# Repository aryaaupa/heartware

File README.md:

# heartware ♥

Heartware is being developed as a custom PCB with real-time audio playback, programmable lighting, sensing, battery power, and low-power firmware. The physical gift is intended to play a user-supplied local copy of **“The Man Who Can't Be Moved” by The Script**; the copyrighted recording is intentionally **not** distributed in this repository. This project will be used to demonstrate basic engineering principles to high schoolers. 

## Project goals

- Heart-shaped custom PCB with the electronics integrated into the board
- ESP32-S3-class embedded controller
- I²S digital audio path and Class-D speaker amplifier
- Local audio playback from flash storage
- Addressable RGB LED perimeter with audio-reactive animation
- Capacitive-touch interaction
- IMU-based pick-up / motion wake behavior
- Li-ion/LiPo battery, charging, battery monitoring, and USB-C power
- Hardware power switch and low-power states
- Debug/test points for board bring-up
- KiCad design sources, BOM, manufacturing outputs, firmware, and validation documentation

## Repository structure

```text
hardware/        KiCad board and schematic sources
firmware/        Embedded firmware and audio pipeline
manufacturing/   BOM / fabrication documentation
docs/            Architecture, bring-up, and validation notes
assets/private/  LOCAL-ONLY audio assets; ignored by Git
```

## Audio asset policy

The public repository contains no copyrighted song recording. A locally obtained audio file can be placed at:

```text
assets/private/song.wav
```

That directory is excluded by `.gitignore`. The firmware/build pipeline will be developed to preprocess and embed or stream the local asset without committing it.

## Status

**Rev A** is the initial KiCad prototype and uses a simpler XIAO ESP32-C3 + I²S amplifier architecture. **Rev B** is the planned advanced redesign described above and will replace the prototype architecture before fabrication.

> Do not fabricate Rev A yet. Footprints, power design, battery circuitry, audio chain, and Rev B architecture still require design review and DRC/ERC validation.

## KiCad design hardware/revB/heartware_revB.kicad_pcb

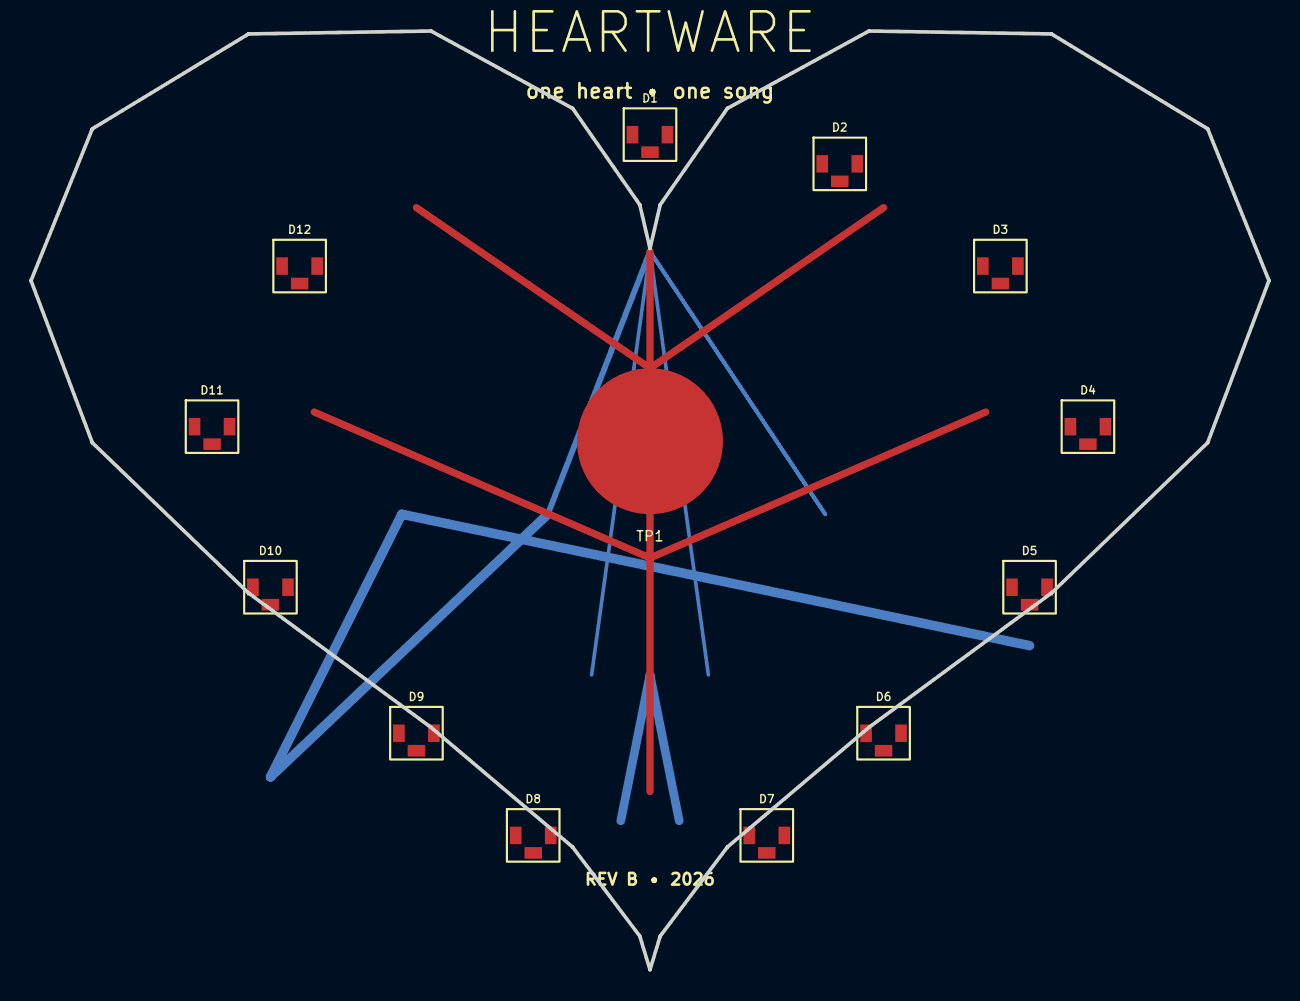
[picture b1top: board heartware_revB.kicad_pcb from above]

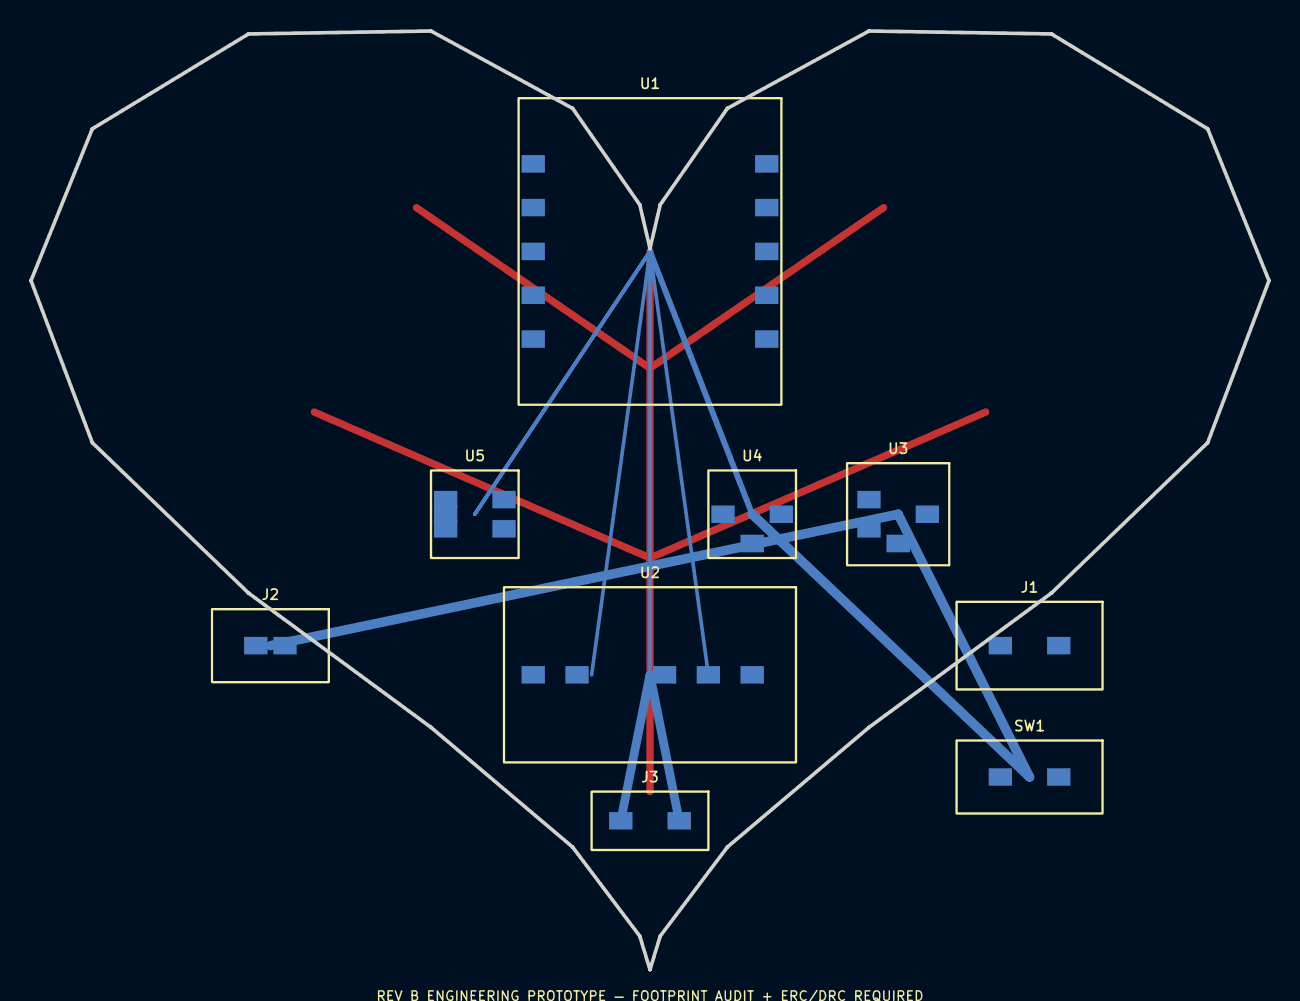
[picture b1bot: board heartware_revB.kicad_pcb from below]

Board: 4 copper layers, 84.8 x 64.3 mm, 22 parts (9 on the bottom side), 14 nets.

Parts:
D1: D1
D2: D2
D3: D3
D4: D4
D5: D5
D6: D6
D7: D7
D8: D8
D9: D9
D10: D10
D11: D11
D12: D12
J1: USB-C CHARGE; J1
J2: LIPO; J2
J3: SPEAKER; J3
SW1: POWER; SW1
TP1: TOUCH
U1: XIAO ESP32-S3; U1
U2: MAX98357A; U2
U3: MCP73871; U3
U4: TPS63031; U4
U5: LIS3DH; U5

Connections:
3V3: U1.3V3, U4.3V3, U5.3V3
BAT+: J2.+, U3.BAT
GND: D1.G, D2.G, D3.G, D4.G, D5.G, D6.G, D7.G, D8.G, D9.G, D10.G, D11.G, D12.G, J1.G, J2.-, U1.GND, U2.GND, U3.G, U4.G, U5.G
I2C_SCL: U1.SCL, U5.SCL
I2C_SDA: U1.SDA, U5.SDA
I2S_BCLK: U1.BCLK, U2.BCLK
I2S_DOUT: U1.DOUT, U2.DIN
I2S_WS: U1.WS, U2.WS
IMU_INT: U1.INT, U5.INT
LED_DATA: D1.D, D2.D, D3.D, D4.D, D5.D, D6.D, D7.D, D8.D, D9.D, D10.D, D11.D, D12.D, U1.LED
LED_PWR: D1.V, D2.V, D3.V, D4.V, D5.V, D6.V, D7.V, D8.V, D9.V, D10.V, D11.V, D12.V, SW1.OUT, U2.VIN, U4.IN
SYS_RAW: SW1.IN, U3.OUT
TOUCH: TP1.1, U1.TOUCH
VBUS_5V: J1.5V, U3.IN

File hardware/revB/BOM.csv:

Ref,Qty,Part,Suggested MPN / family,Package / form,Purpose,Prototype note
U1,1,ESP32-S3 controller,Seeed XIAO ESP32-S3,module,"MP3 decode, I2S, touch, LEDs, USB debug","Back-mounted, USB accessible at edge"
U2,1,I2S Class-D amplifier,MAX98357A module,module,Digital audio to speaker,Module keeps Rev B hand-assemblable
U3,1,LiPo charger + power-path,MCP73871-2CCI/ML,QFN-20 4x4,Charge/load sharing,Verify charger resistor values and thermal pad
U4,1,3.3V buck-boost,TPS63031DSK,WSON-10 2.5x2.5,Stable 3.3V rail,Use recommended 2.2uH inductor and ceramics
U5,1,3-axis accelerometer,LIS3DH,LGA-16 3x3,"Pick-up wake, motion interaction",I2C + INT1
D1-D12,12,Addressable RGB LED,SK6812MINI-E,3535 reverse/mini family,Perimeter animations,Confirm exact pin orientation before assembly
J1,1,USB-C receptacle,USB2.0 Type-C power-only family,mid-mount or top-mount,Charging input,Add 5.1k CC1/CC2 Rd resistors
J2,1,LiPo connector,JST-PH-2 vertical/right-angle,2-pin,1S LiPo,Mark polarity on silk + copper
J3,1,Speaker connector,JST-PH-2 or solder pads,2-pin,4-8 ohm speaker,Keep output pair short
SW1,1,Slide switch,SPDT SMD low-profile,SMD,Master system power,Placed at lower-left edge
SPK1,1,Mini speaker,8 ohm 1W 28-40mm,off-board,Audio output,Mount behind board or in printed stand
BAT1,1,Protected LiPo,1S 3.7V 500-1000mAh,off-board,Portable power,Use protected cell for first build

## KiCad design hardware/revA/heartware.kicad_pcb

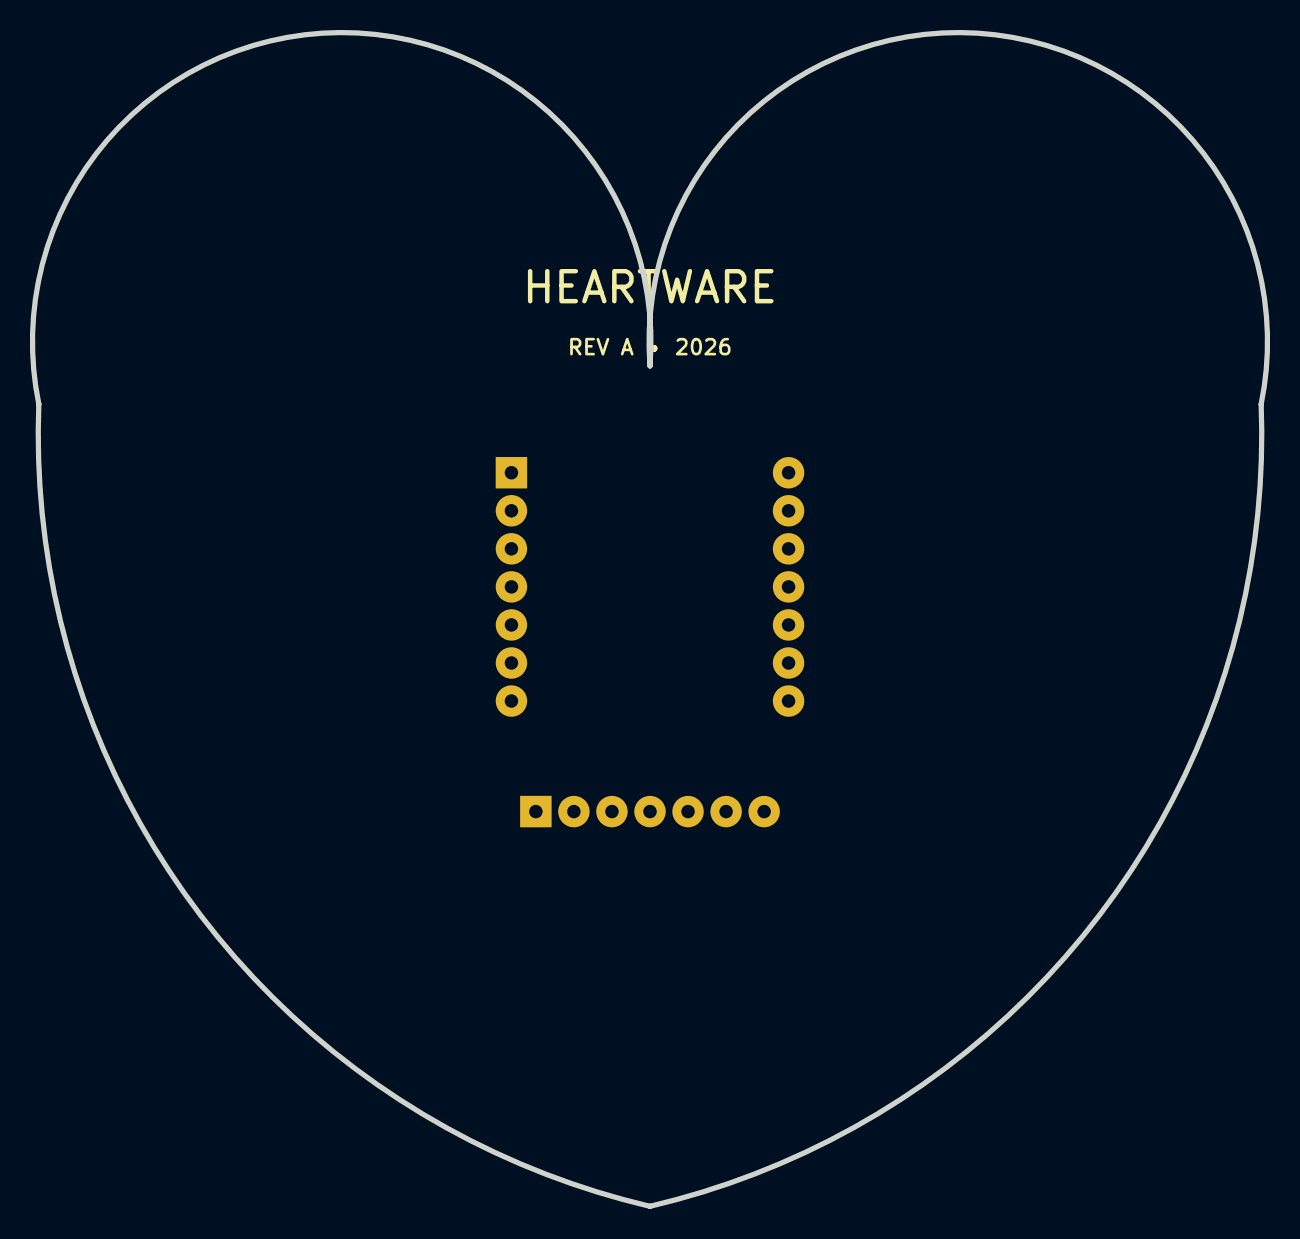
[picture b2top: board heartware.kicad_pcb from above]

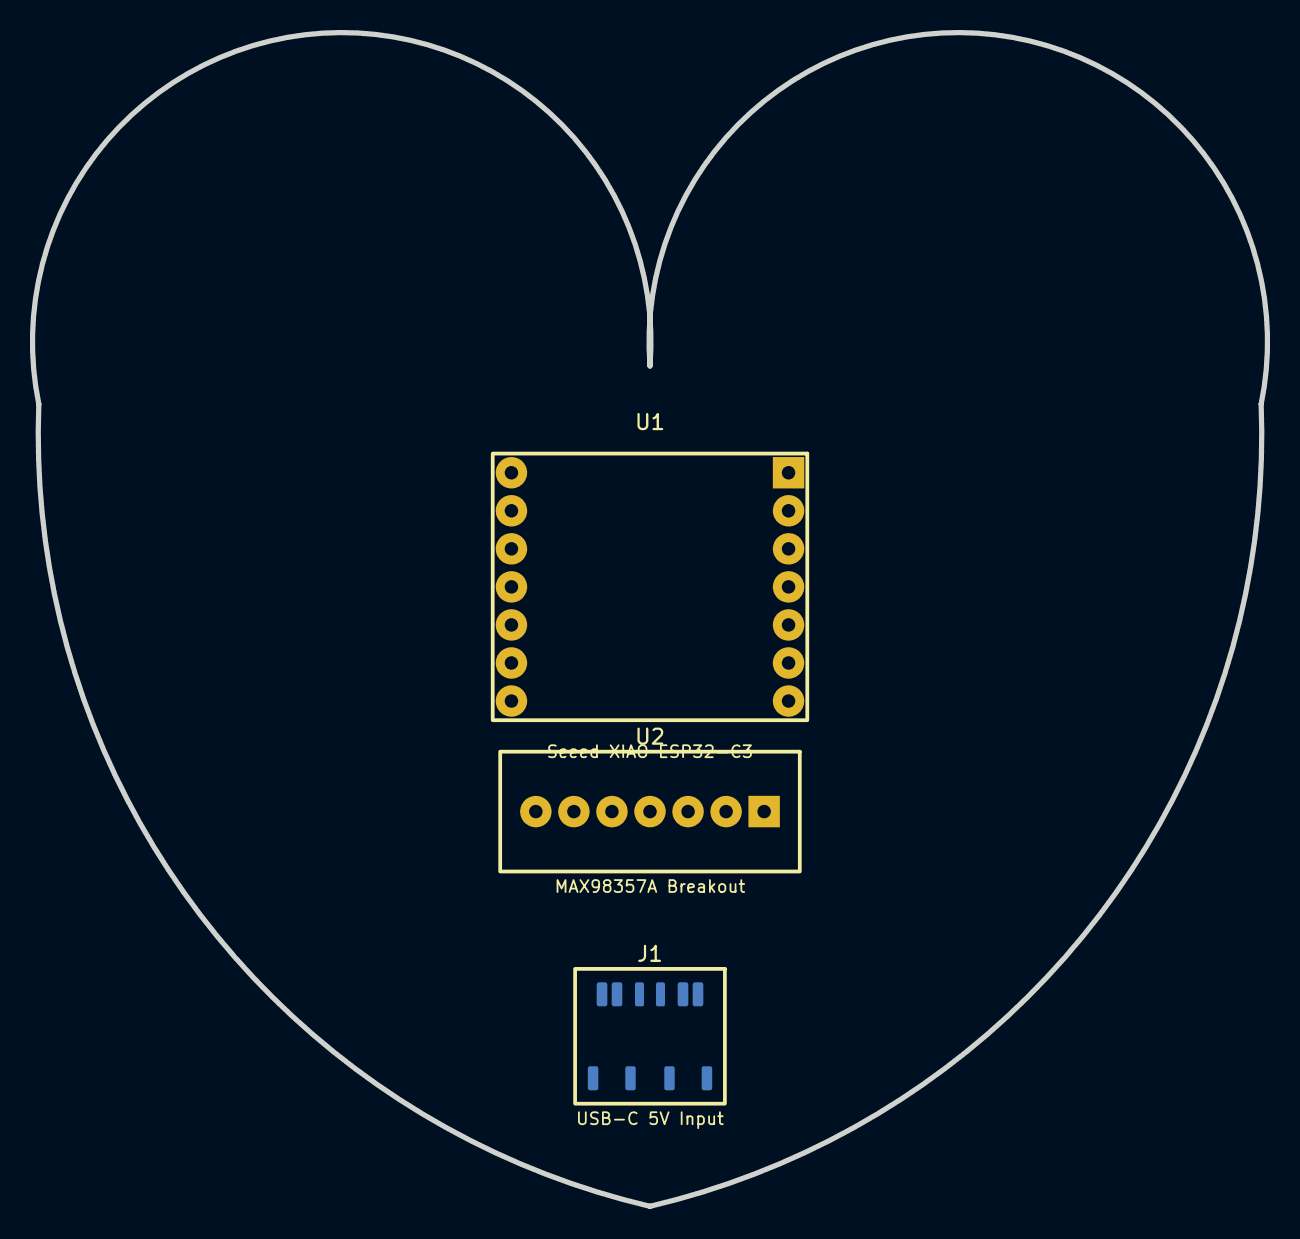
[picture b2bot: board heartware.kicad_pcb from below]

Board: 2 copper layers, 82.4 x 78.4 mm, 3 parts (3 on the bottom side), 6 nets, no tracks yet.

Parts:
J1: USB-C 5V Input; USB_C_POWER_ONLY
U1: Seeed XIAO ESP32-C3; XIAO_ESP32C3
U2: MAX98357A Breakout; MAX98357A_BREAKOUT

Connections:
5V_SYS: U1.14, U2.7
GND: J1.A1, J1.A12, J1.B1, J1.B12, U1.13, U2.6
I2S_BCLK: U1.7, U2.2
I2S_DIN: U1.8, U2.3
I2S_LRC: U1.6, U2.1
VBUS_IN: J1.A4, J1.A9, J1.B4, J1.B9
